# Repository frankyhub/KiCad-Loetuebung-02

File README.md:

<div align="center">

|[:skull:ISSUE](https://github.com/frankyhub/KiCad-Loetuebung-02/issues?q=is%3Aissue)|[:speech_balloon: Forum /Discussion](https://github.com/frankyhub/KiCad-Loetuebung-02/discussions)|[:grey_question:WiKi](https://github.com/frankyhub/KiCad-Loetuebung-02/wiki)||
|--|--|--|--|
| | | | |
||<a href="https://github.com/frankyhub/KiCad-Loetuebung-02/issues">|<a href="https://github.com/frankyhub/KiCad-Loetuebung-02/discussions">|<a href="https://github.com/frankyhub/KiCad-Loetuebung-02/releases">|
|| <a href="https://github.com/frankyhub/KiCad-Loetuebung-02/pulse" alt="Activity">| <a href="https://github.com/frankyhub/KiCad-Loetuebung-02/graphs/traffic">  |<a href="https://github.com/frankyhub?tab=stars"> |
</div>

# KiCad-Loetuebung-02
NE555 Platinen, zwei LEDs

## BOM

| Anzahl | Bezeichnung | 
| -------- | -------- | 
| 1  |  Platine	  |
|  1 | Batteriehalter	   |
| 1  | CR2032	   |
| 1  |  Schalter  |
| 1  |  NE555	  |
| 1  |  R1off1	12K  |
| 1 | R2on2	16K  |
| 1  |  R3	560k  |
| 1  | R4	390k   | 
| 1  |  R5	4k7  | 
|  1 | R6	10R  | 
|  1 |  D3	1N4148  | 
| 2  |  Q1, Q2	BC548  | 
|  2 |   D1, D2	LED rt 3mm| 
|  1 |  C1	47uF | 
| -------- | -------- | 

|	               |Löten I  |Löten II 	   |Löten III|
|--|--|--|--|
|1 x Platine		|:white_check_mark:|:white_check_mark:|:white_check_mark:|
|1 x Batteriehalter 9V  |:white_check_mark:|:x:|:x:|
|1 x Batterie 9V        |:white_check_mark:|:x:|:x:|
|1 x Batteriehalter CR2032 |:x:	|:white_check_mark:|:white_check_mark:|
|1 x CR2032		|:x:|:white_check_mark:|:white_check_mark:|
|1 x Schalter		|:x:|:white_check_mark:|:white_check_mark:|
|1 x NE555		|:x:|:white_check_mark:|:white_check_mark:|
|1 x R1	12k		|:x:|:white_check_mark:|:x:|
|1 x R2	16k		|:x:|:white_check_mark:|:x:|
|1 x R3	560k		|:x:|:white_check_mark:|:white_check_mark:|
|1 x R4	390k		|:x:|:white_check_mark:|:white_check_mark:|
|4 x 10k		|:white_check_mark:|:x:|:x:|
|1 x R5	4k7		|:x:|:white_check_mark:|:white_check_mark:|
|4 x 470R		|:white_check_mark:|:x:|:x:|
|1 x R6	10R		|:x:|:white_check_mark:|:white_check_mark:|
|1 x D3	1N4148		|:x:|:white_check_mark:|:white_check_mark:|
|4 x BC548		|:white_check_mark:|:x:|:x:|
|2 x Q1, Q2 BC548	|:x:|:white_check_mark:|:white_check_mark:|
|2 x D1, D2 LED	5mm	|:x:|:white_check_mark:|:x:|
|4 x LED 5mm		|:white_check_mark:|:x:|:x:|
|4 x 100uF		|:white_check_mark:|:x:|:x:|
|1 x C1	47uF		|:x:|:white_check_mark:|:white_check_mark:|
|2 x Trimmer 10k	|:x:|:x:|:white_check_mark:|
|10 x LED 3mm		|:x:|:x:|:white_check_mark:|
|                       |~10,-|~10,-|~12,-|

---
Beispiele

---

<div style="position:absolute; left:2cm; ">   
<ol class="breadcrumb" style="border-top: 2px solid black;border-bottom:2px solid black; height: 45px; width: 900px;"> <p align="center"><a href="#oben">nach oben</a></p></ol>
</div>  

---

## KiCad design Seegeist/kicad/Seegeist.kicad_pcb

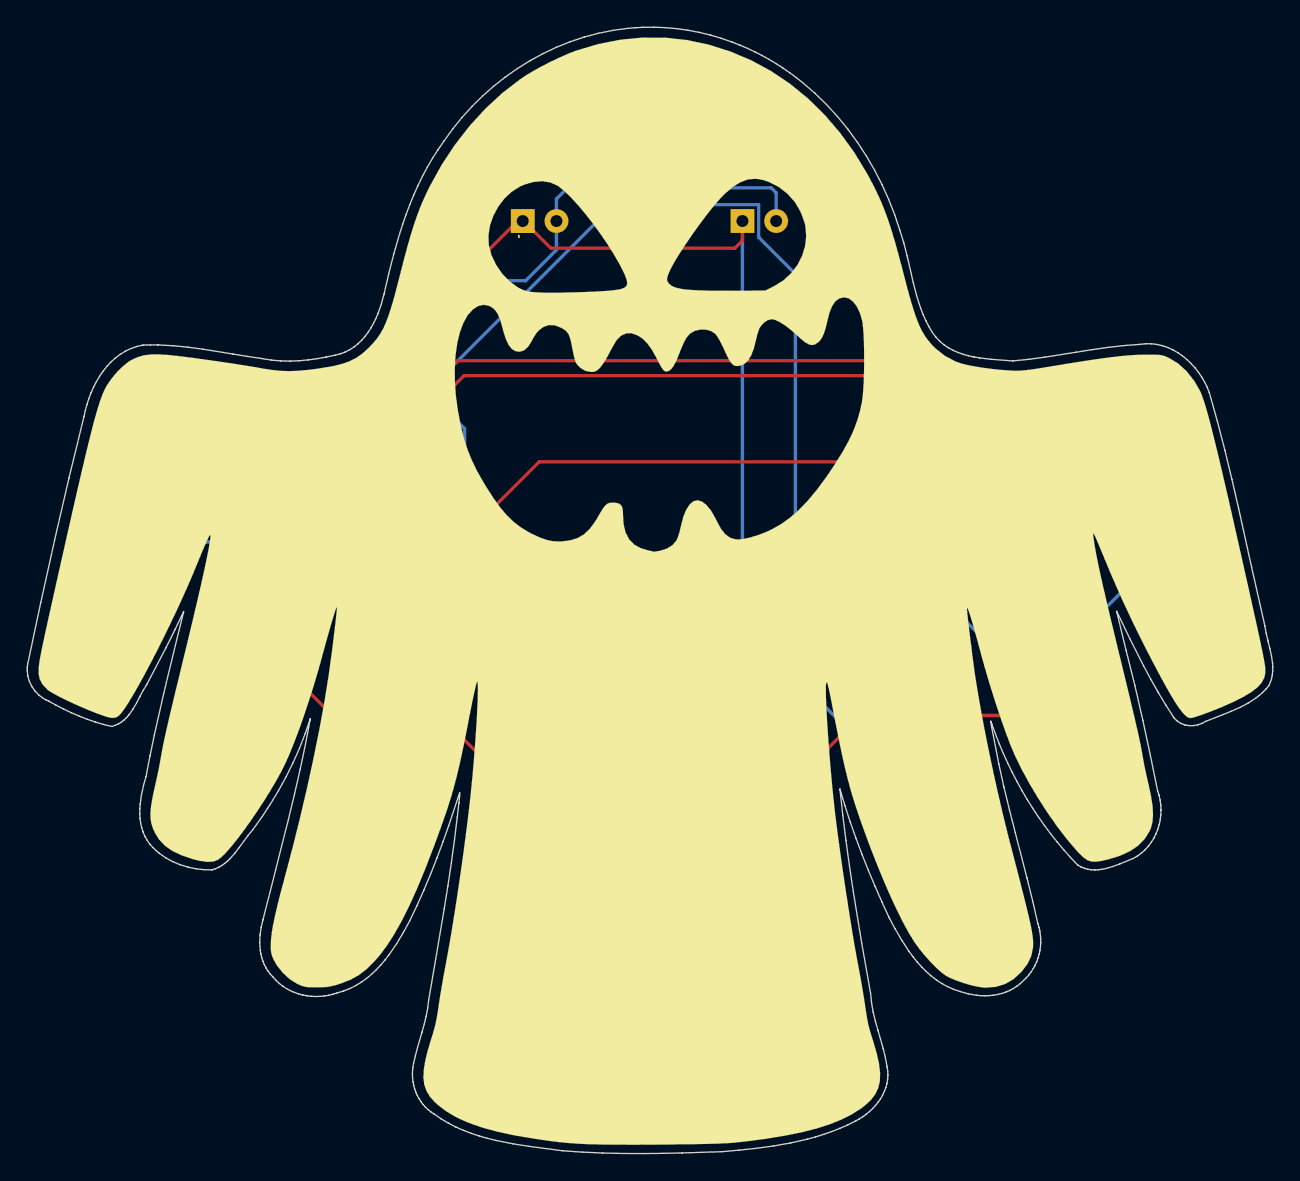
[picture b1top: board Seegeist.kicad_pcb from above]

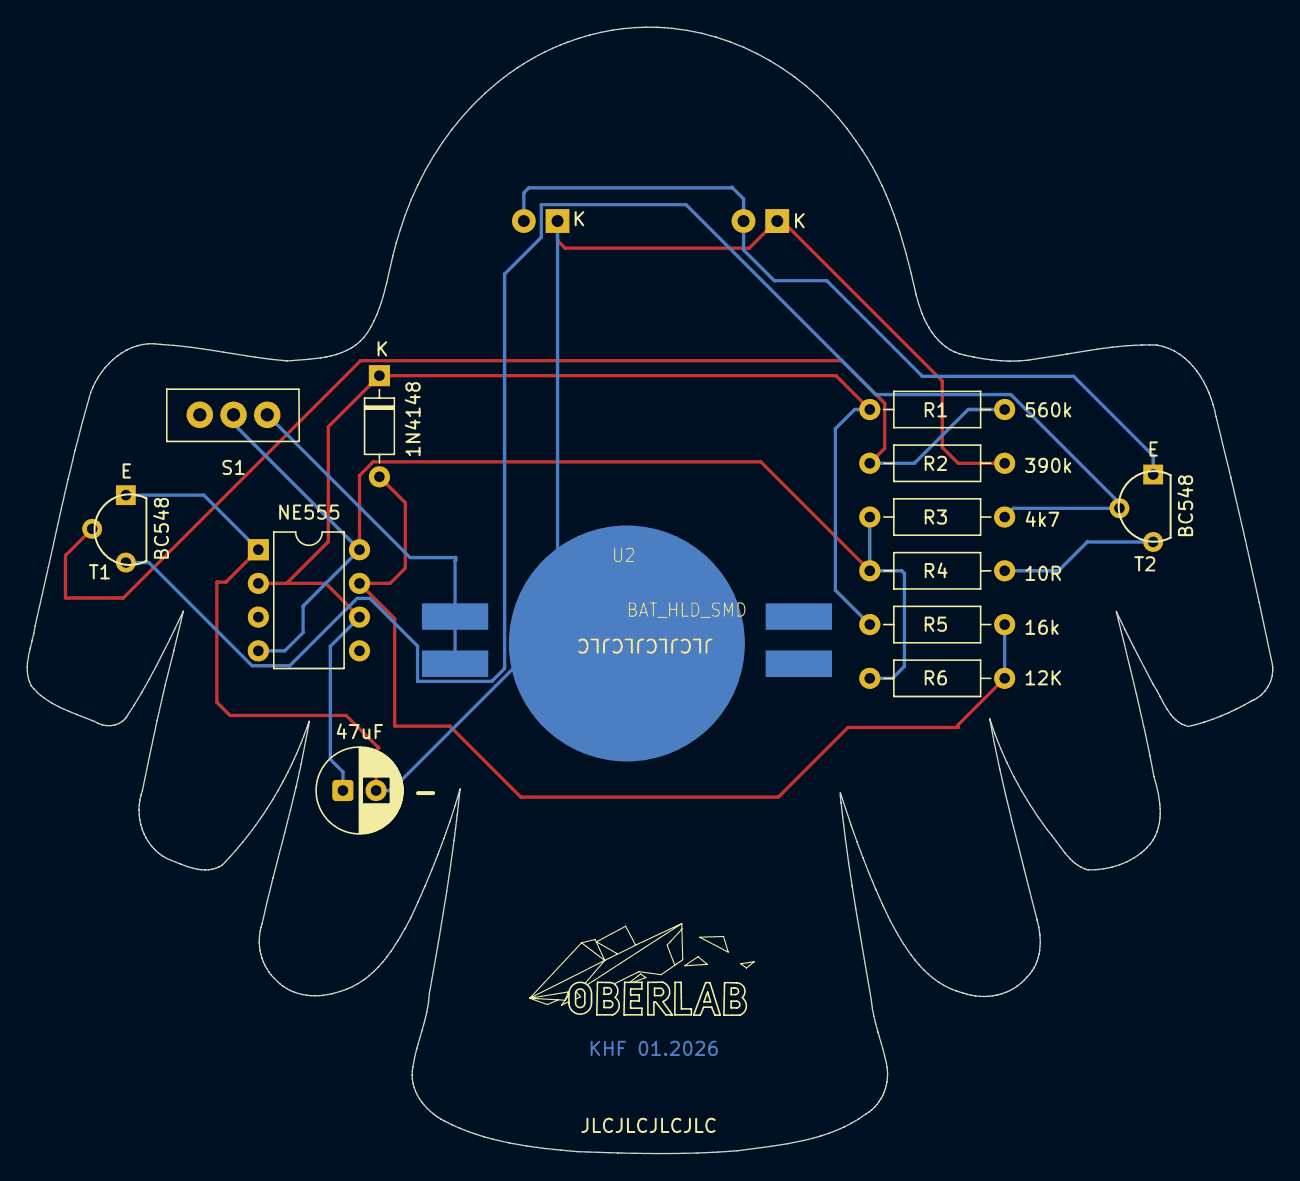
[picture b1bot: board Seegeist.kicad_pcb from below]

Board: 2 copper layers, 93.8 x 84.9 mm, 15 parts (11 on the bottom side), 9 nets.

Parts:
47uF: 47uF; CP_Radial_D6.3mm_P2.50mm
D1, D2: LED; LED_D3.0mm
D3: 1N4148; 1N4147_P7.62mm_Horizontal
NE555: NE555P; DIP-8_W7.62mm
Q1, Q2: Q_NPN_EBC; TO-92L_Wide
R3: 4k7; R_Axial_DIN0207_L6.3mm_D2.5mm_P10.16mm_Horizontal
R4: 390k; R_Axial_DIN0207_L6.3mm_D2.5mm_P10.16mm_Horizontal
R4#2: 560k; R_Axial_DIN0207_L6.3mm_D2.5mm_P10.16mm_Horizontal
R4#3: 10R; R_Axial_DIN0207_L6.3mm_D2.5mm_P10.16mm_Horizontal
R5: 16K; R_Axial_DIN0207_L6.3mm_D2.5mm_P10.16mm_Horizontal
R6: 12K; R_Axial_DIN0207_L6.3mm_D2.5mm_P10.16mm_Horizontal
S1: Micro_Schalter; Micro_SchalterKHF
U2: BAT_HLD_SMD; BAT-HLD-SMD-Blech

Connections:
unnamed: D1.2 (A), D2.2 (A), Q2.1 (E)
unnamed: 47uF.2, D1.1 (K), D2.1 (K), NE555.1 (GND), Q1.1 (E), R4.2, U2.2
unnamed: D3.2 (A), NE555.7 (DIS), R5.2, R6.2
unnamed: 47uF.1, D3.1 (K), NE555.2 (TR), NE555.6 (THR), R4#2.1, R5.1
unnamed: Q1.2 (B), R4.1, R4#2.2
unnamed: Q1.3 (C), Q2.2 (B), R3.2
unnamed: Q2.3 (C), R4#3.2
unnamed: S1.1 (A), U2.1
unnamed: NE555.4 (R), NE555.8 (VCC), R3.1, R4#3.1, R6.1, S1.2 (E)

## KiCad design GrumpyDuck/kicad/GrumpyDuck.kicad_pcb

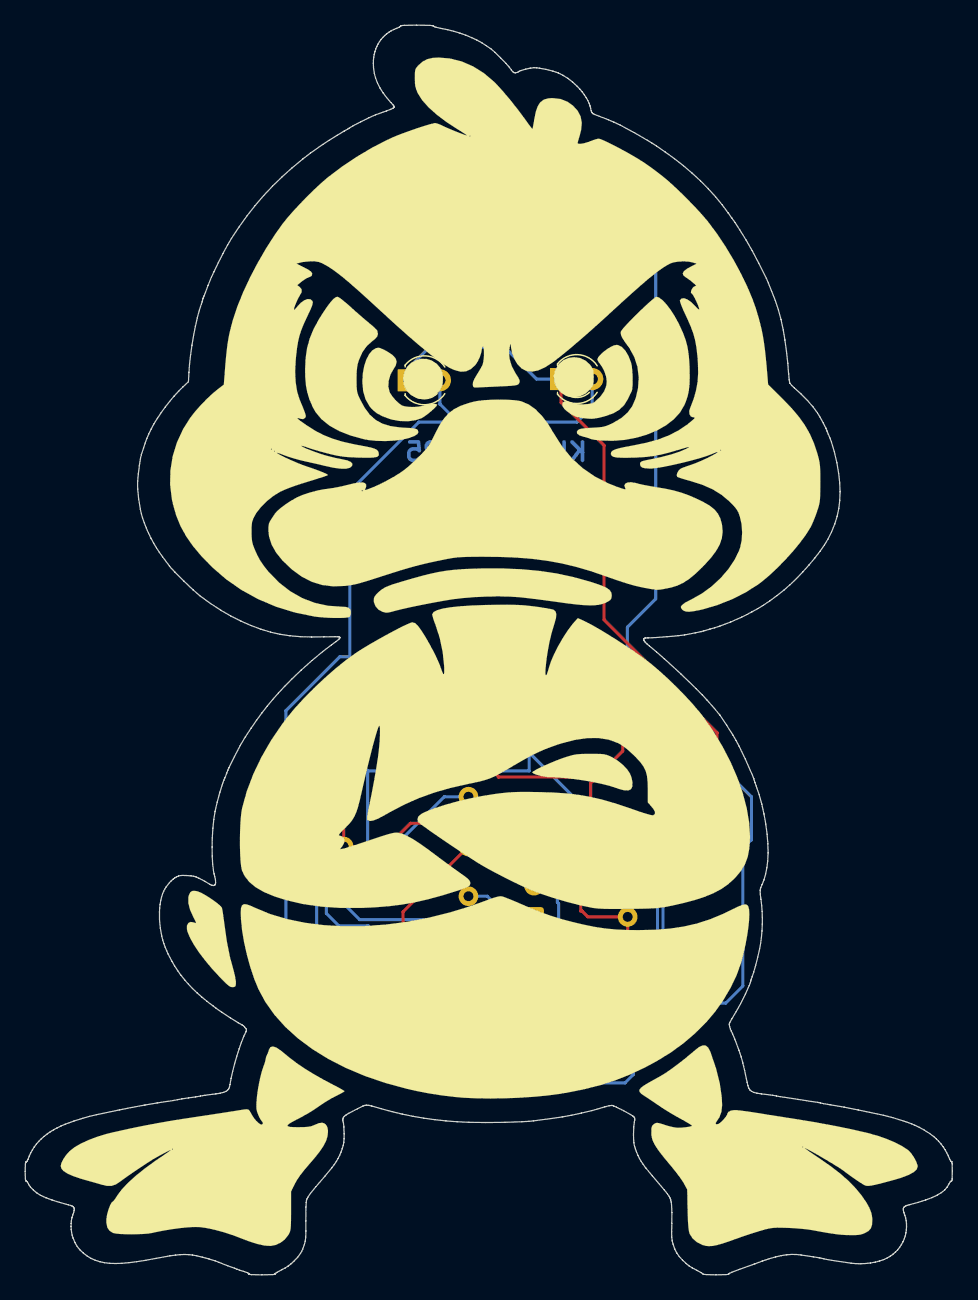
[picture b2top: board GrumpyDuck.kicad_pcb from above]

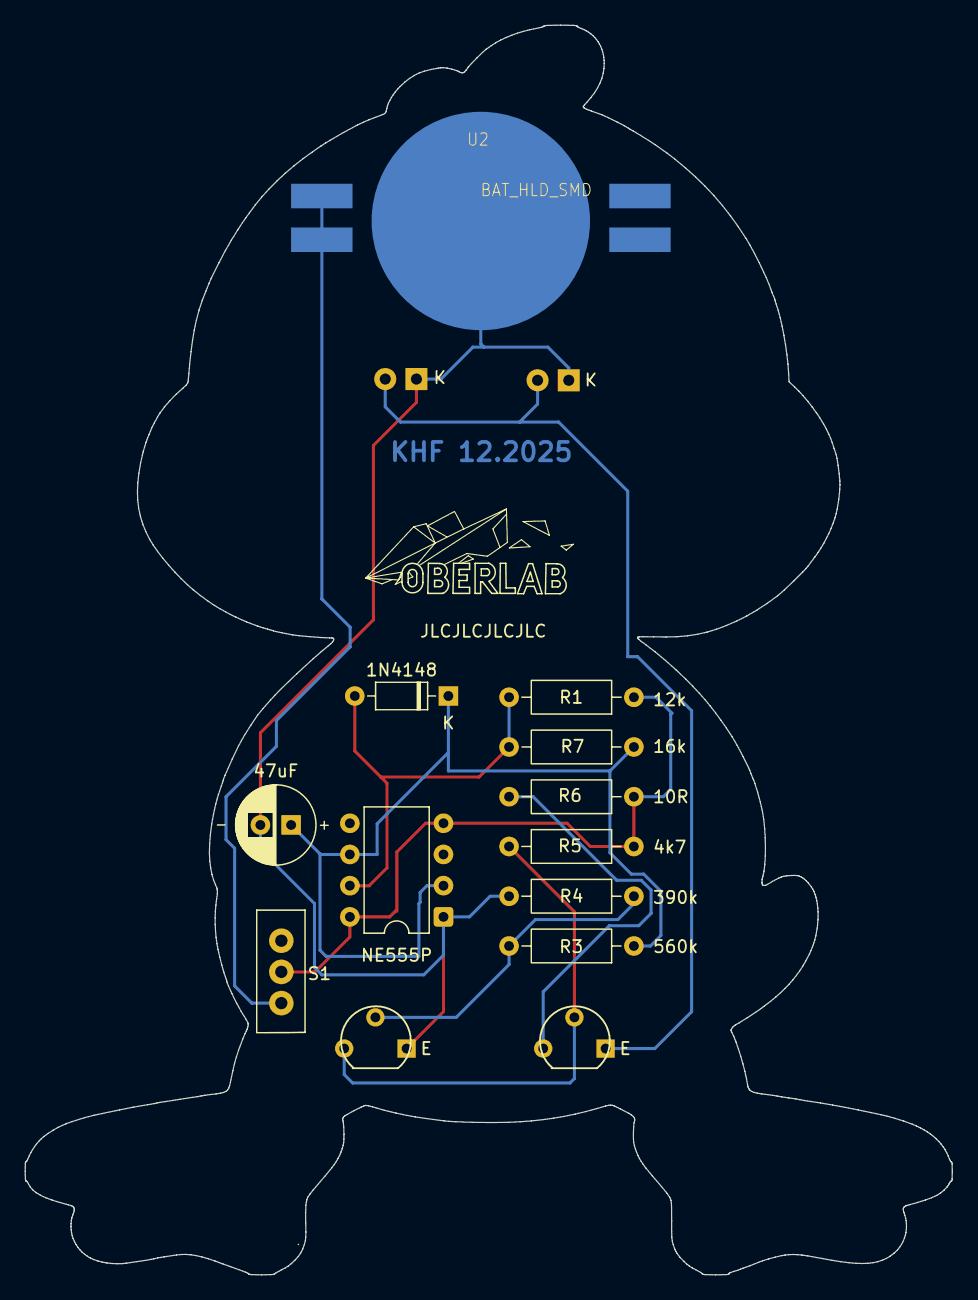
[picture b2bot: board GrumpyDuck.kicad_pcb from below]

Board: 2 copper layers, 75.5 x 101.7 mm, 15 parts (11 on the bottom side), 9 nets.

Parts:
C1: 47uF; C_Radial_D6.3mm_P2.50mm
D1, D2: LED; LED_D3.0mm
D3: 1N4148; 1N4147_P7.62mm_Horizontal
R1: 12k; R_Axial_DIN0207_L6.3mm_D2.5mm_P10.16mm_Horizontal
R3: 560k; R_Axial_DIN0207_L6.3mm_D2.5mm_P10.16mm_Horizontal
R4: 390k; R_Axial_DIN0207_L6.3mm_D2.5mm_P10.16mm_Horizontal
R5: 4k7; R_Axial_DIN0207_L6.3mm_D2.5mm_P10.16mm_Horizontal
R6: 10R; R_Axial_DIN0207_L6.3mm_D2.5mm_P10.16mm_Horizontal
R7: 16k; R_Axial_DIN0207_L6.3mm_D2.5mm_P10.16mm_Horizontal
S1: Micro_Schalter; Micro_SchalterKHF
T1, T2: Q_NPN_EBC; TO-92L_Wide
U1: NE555P; DIP-8_W7.62mm
U2: BAT_HLD_SMD; BAT-HLD-SMD-Blech

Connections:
unnamed: D1.2 (A), D2.2 (A), T2.1 (E)
unnamed: C1.2, D1.1 (K), D2.1 (K), R4.2, T1.1 (E), U1.1 (GND), U2.2
unnamed: D3.2 (A), R1.2, R7.2, U1.7 (DIS)
unnamed: C1.1, D3.1 (K), R3.1, R7.1, U1.2 (TR), U1.6 (THR)
unnamed: R3.2, R4.1, T1.2 (B)
unnamed: R5.2, T1.3 (C), T2.2 (B)
unnamed: R6.2, T2.3 (C)
unnamed: S1.1 (A), U2.1
unnamed: R1.1, R5.1, R6.1, S1.2 (E), U1.4 (R), U1.8 (VCC)

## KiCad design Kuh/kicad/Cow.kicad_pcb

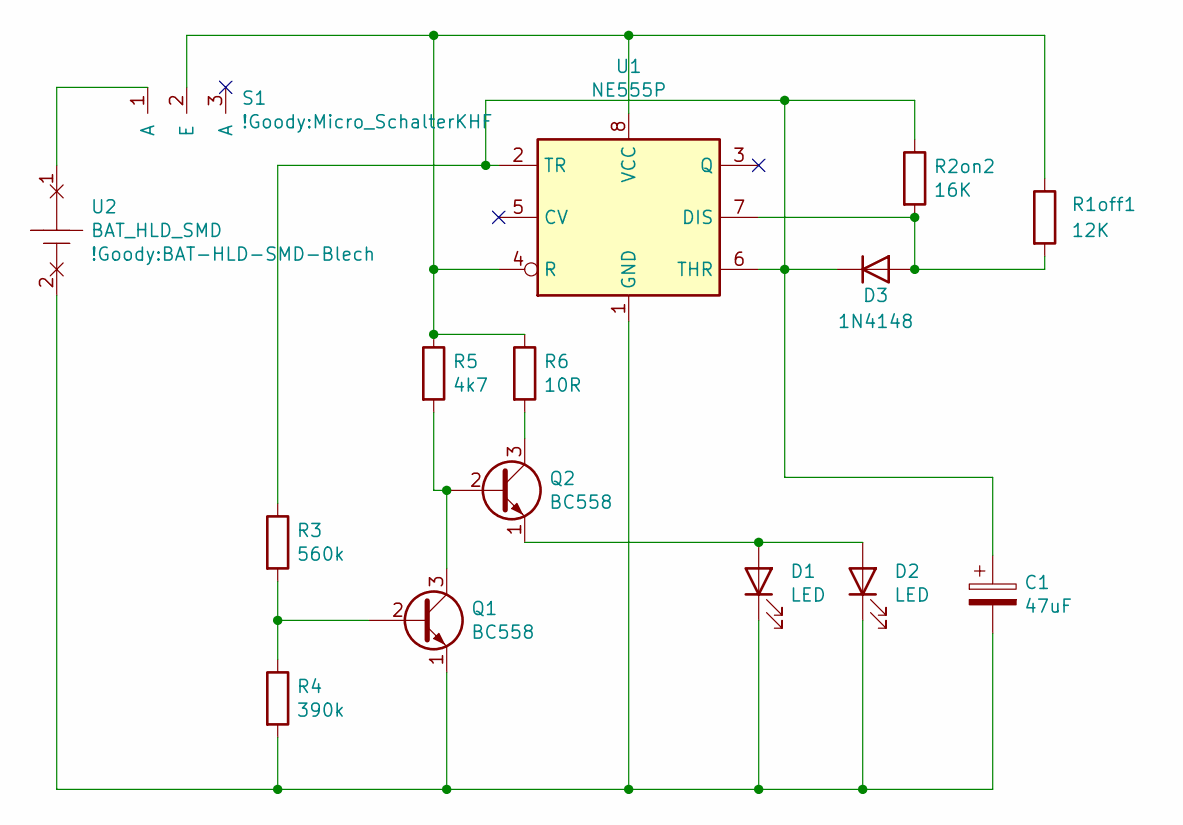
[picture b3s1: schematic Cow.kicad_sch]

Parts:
C1: 47uF; CP_Radial_D6.3mm_P2.50mm
D1, D2: LED; LED_D5.0mm
D3: 1N4148; D_DO-35_SOD27_P7.62mm_Horizontal
Q1, Q2: BC558; TO-92L_Wide
R1off1: 12K; R_Axial_DIN0207_L6.3mm_D2.5mm_P10.16mm_Horizontal
R2on2: 16K; R_Axial_DIN0207_L6.3mm_D2.5mm_P10.16mm_Horizontal
R3: 560k; R_Axial_DIN0207_L6.3mm_D2.5mm_P10.16mm_Horizontal
R4: 390k; R_Axial_DIN0207_L6.3mm_D2.5mm_P10.16mm_Horizontal
R5: 4k7; R_Axial_DIN0207_L6.3mm_D2.5mm_P10.16mm_Horizontal
R6: 10R; R_Axial_DIN0207_L6.3mm_D2.5mm_P10.16mm_Horizontal
S1: Micro_Schalter; Micro_SchalterKHF
U1: NE555P; DIP-8_W7.62mm
U2: BAT_HLD_SMD; BAT-HLD-SMD-Blech

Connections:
unnamed: D1.2 (A), D2.2 (A), Q2.1 (E)
unnamed 1: C1.2, D1.1 (K), D2.1 (K), Q1.1 (E), R4.2, U1.1 (GND), U2.2; also elsewhere on the board
unnamed 2: D3.2 (A), R1off1.2, U1.7 (DIS); also elsewhere on the board
unnamed 3: C1.1, D3.1 (K), R3.1, U1.2 (TR), U1.6 (THR); also elsewhere on the board
unnamed: Q1.2 (B), R3.2, R4.1
unnamed: Q1.3 (C), Q2.2 (B), R5.2
unnamed: Q2.3 (C), R6.2
unnamed: S1.1 (A), U2.1
unnamed: R1off1.1, R5.1, R6.1, S1.2 (E), U1.4 (R), U1.8 (VCC)

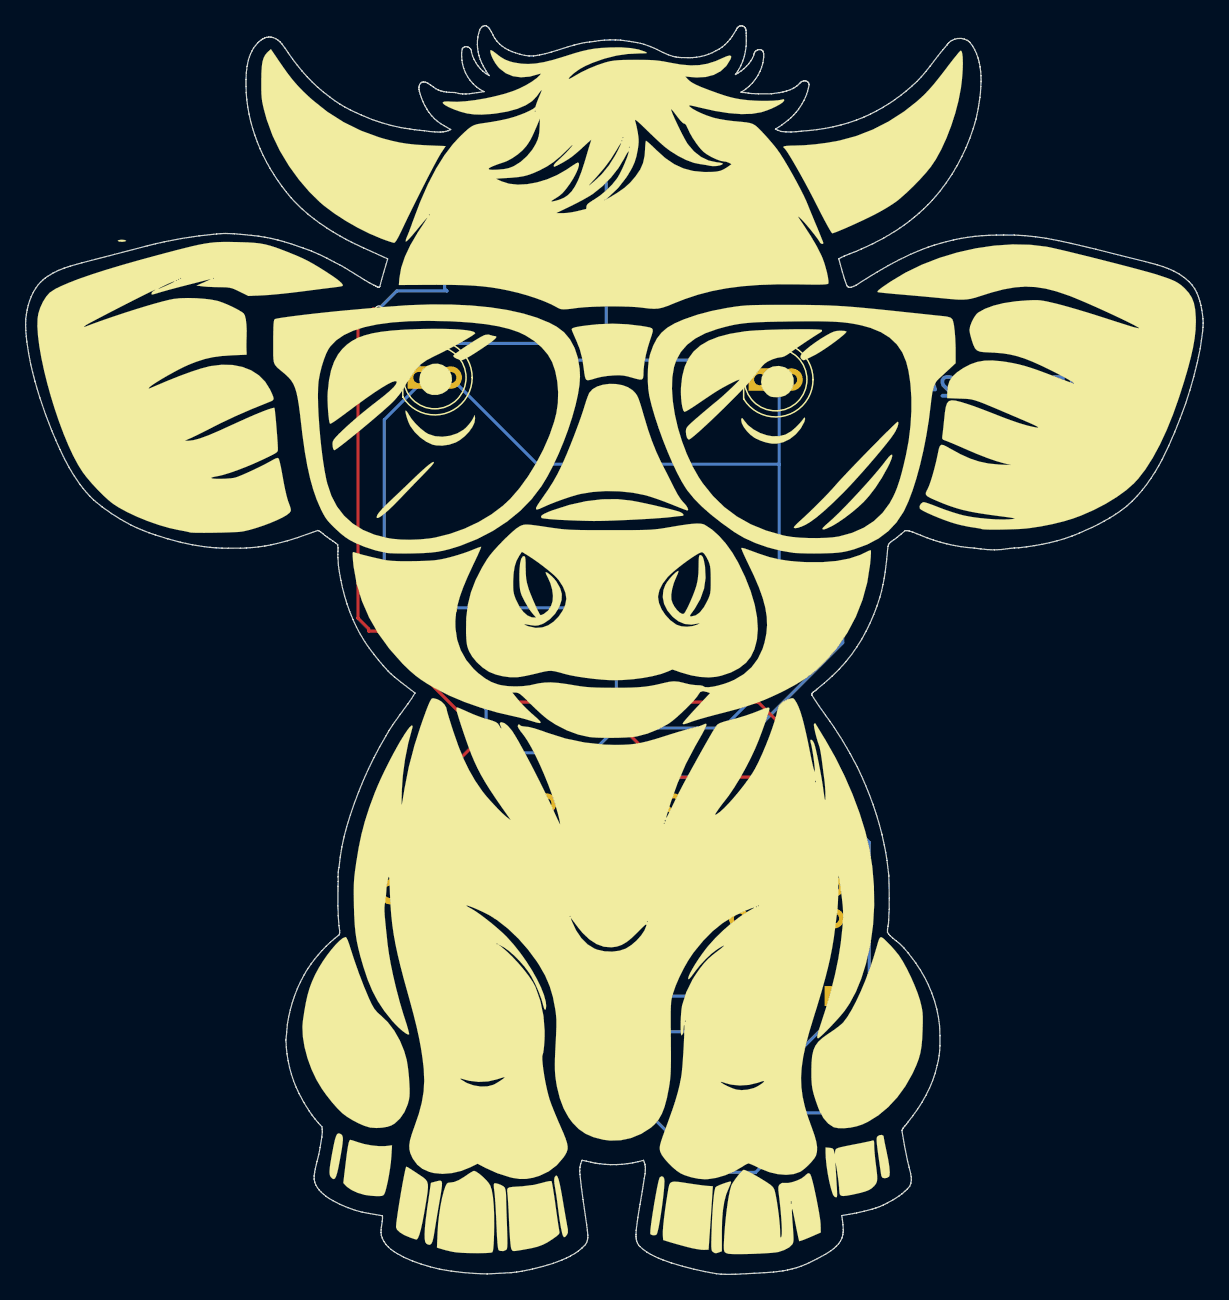
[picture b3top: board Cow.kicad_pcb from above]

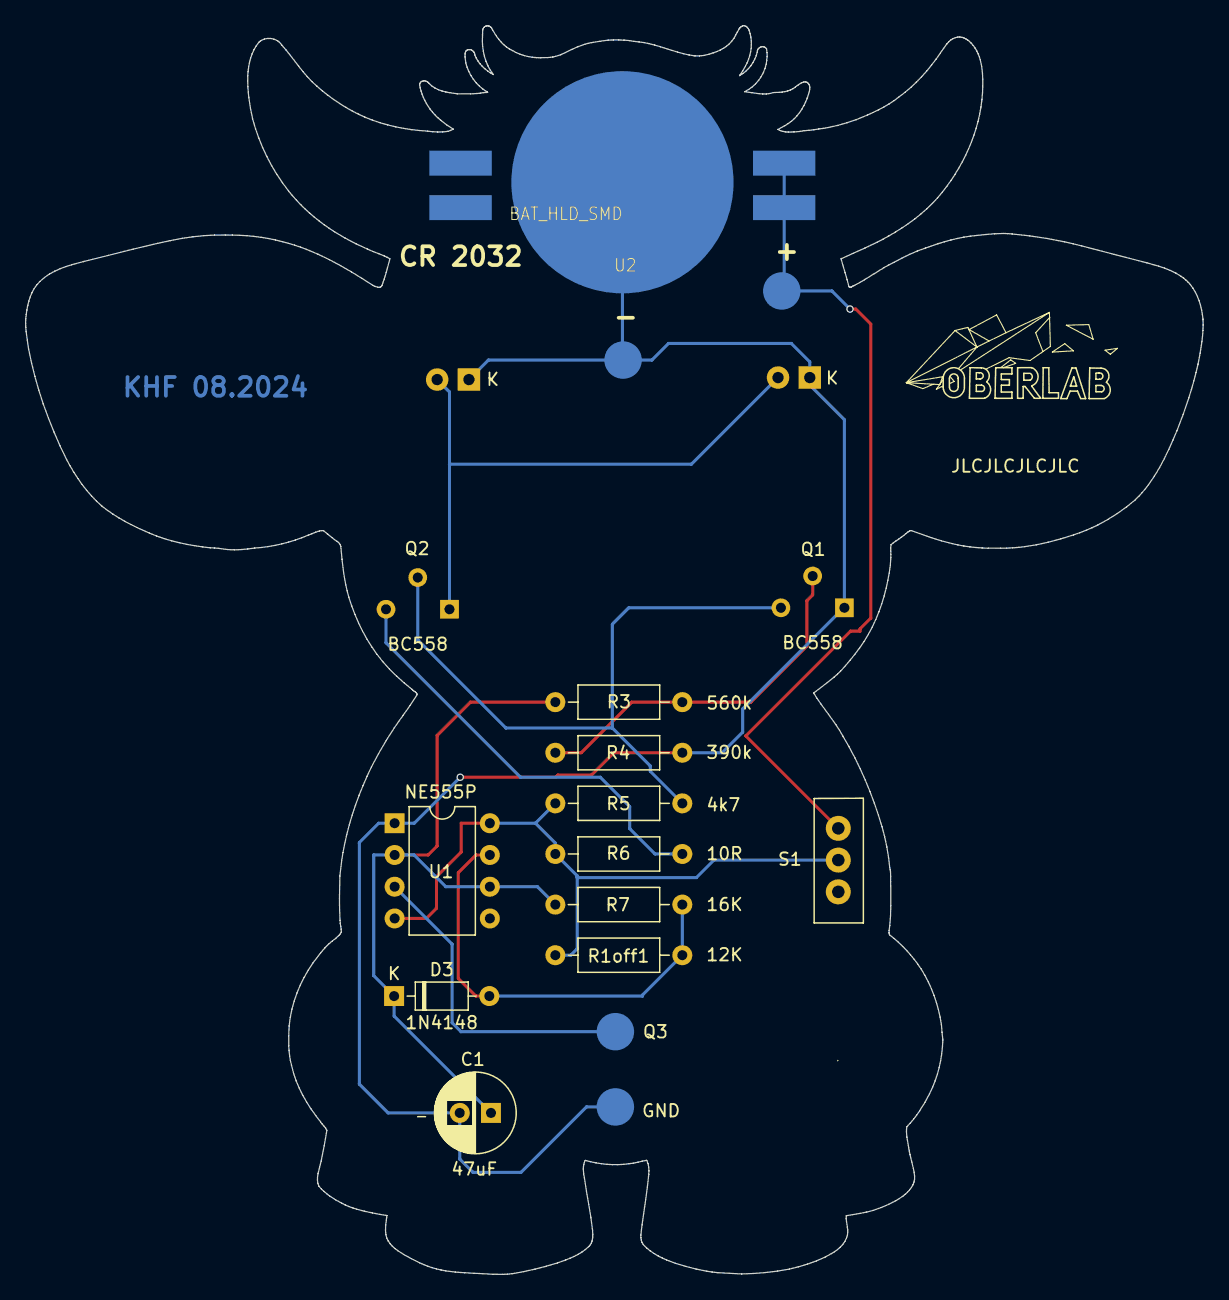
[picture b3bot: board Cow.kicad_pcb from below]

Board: 2 copper layers, 94.2 x 99.9 mm, 16 parts (12 on the bottom side), 9 nets.

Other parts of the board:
+: LP
R7: 16K; R_Axial_DIN0207_L6.3mm_D2.5mm_P10.16mm_Horizontal

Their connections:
unnamed 1: +.1; also elsewhere on the board
unnamed 2: R7.2; also elsewhere on the board
unnamed 3: R7.1; also elsewhere on the board

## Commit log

2024-02-27 V 01.2025
2024-02-27 V 01.2024
2024-02-27 V 1.2024
2024-02-27 BOM Update README.md
2024-02-27 LED 3mm Update README.md
2024-04-02 V1.2 02.04.2024
2024-06-20 V 20.06.2024
2024-08-03 V 03082024
2024-08-08 V 08082024_
2024-08-10 V 10081024
2024-08-22 V 22.08.2024
2024-09-10 V 10092024
2024-09-22 V 22092024
2024-10-12 V12102024
2025-03-31 V31032025
2025-11-30 V30112025
2025-12-01 V01122025
2025-12-04 V04122025
2025-12-04 V04122025
    Added examples section with an image to README.
2025-12-04 V03122025
2025-12-04 V04122025
    Added additional images of a penguin and a koala to the examples section.
2025-12-05 V05122025
2025-12-06 V06122025
2025-12-07 V07122025
2025-12-08 V08122025
2025-12-08 V0812205
2025-12-10 V10122025
2025-12-10 V101212025
2025-12-13 V13122025
2025-12-18 V18122025
2025-12-30 V30122025
2026-01-03 V03012026
2026-01-09 V09012026
2026-01-09 V09012026
    Added description for USB 3.1 Type C connector.
2026-01-10 V10012026
2026-01-10 V10012026
    Add images to README for visual representation
2026-01-23 V23012026
2026-01-23 V23012025
2026-01-25 V25012026
2026-01-25 V26012026
2026-01-25 25012026
2026-05-12 V12052026
